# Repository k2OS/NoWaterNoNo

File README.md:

<h1>No Water, No No</h1>
See https://labitat.dk/wiki/No_Water_No_No for more information.

Eagle/ contains eagle files for the PCB

OpenSCAD/ contains the OpenSCAD drawings for the mounting brackets for the nodes + the battery compartment.

NoWaterNoNo/ contains the software for the nodes.

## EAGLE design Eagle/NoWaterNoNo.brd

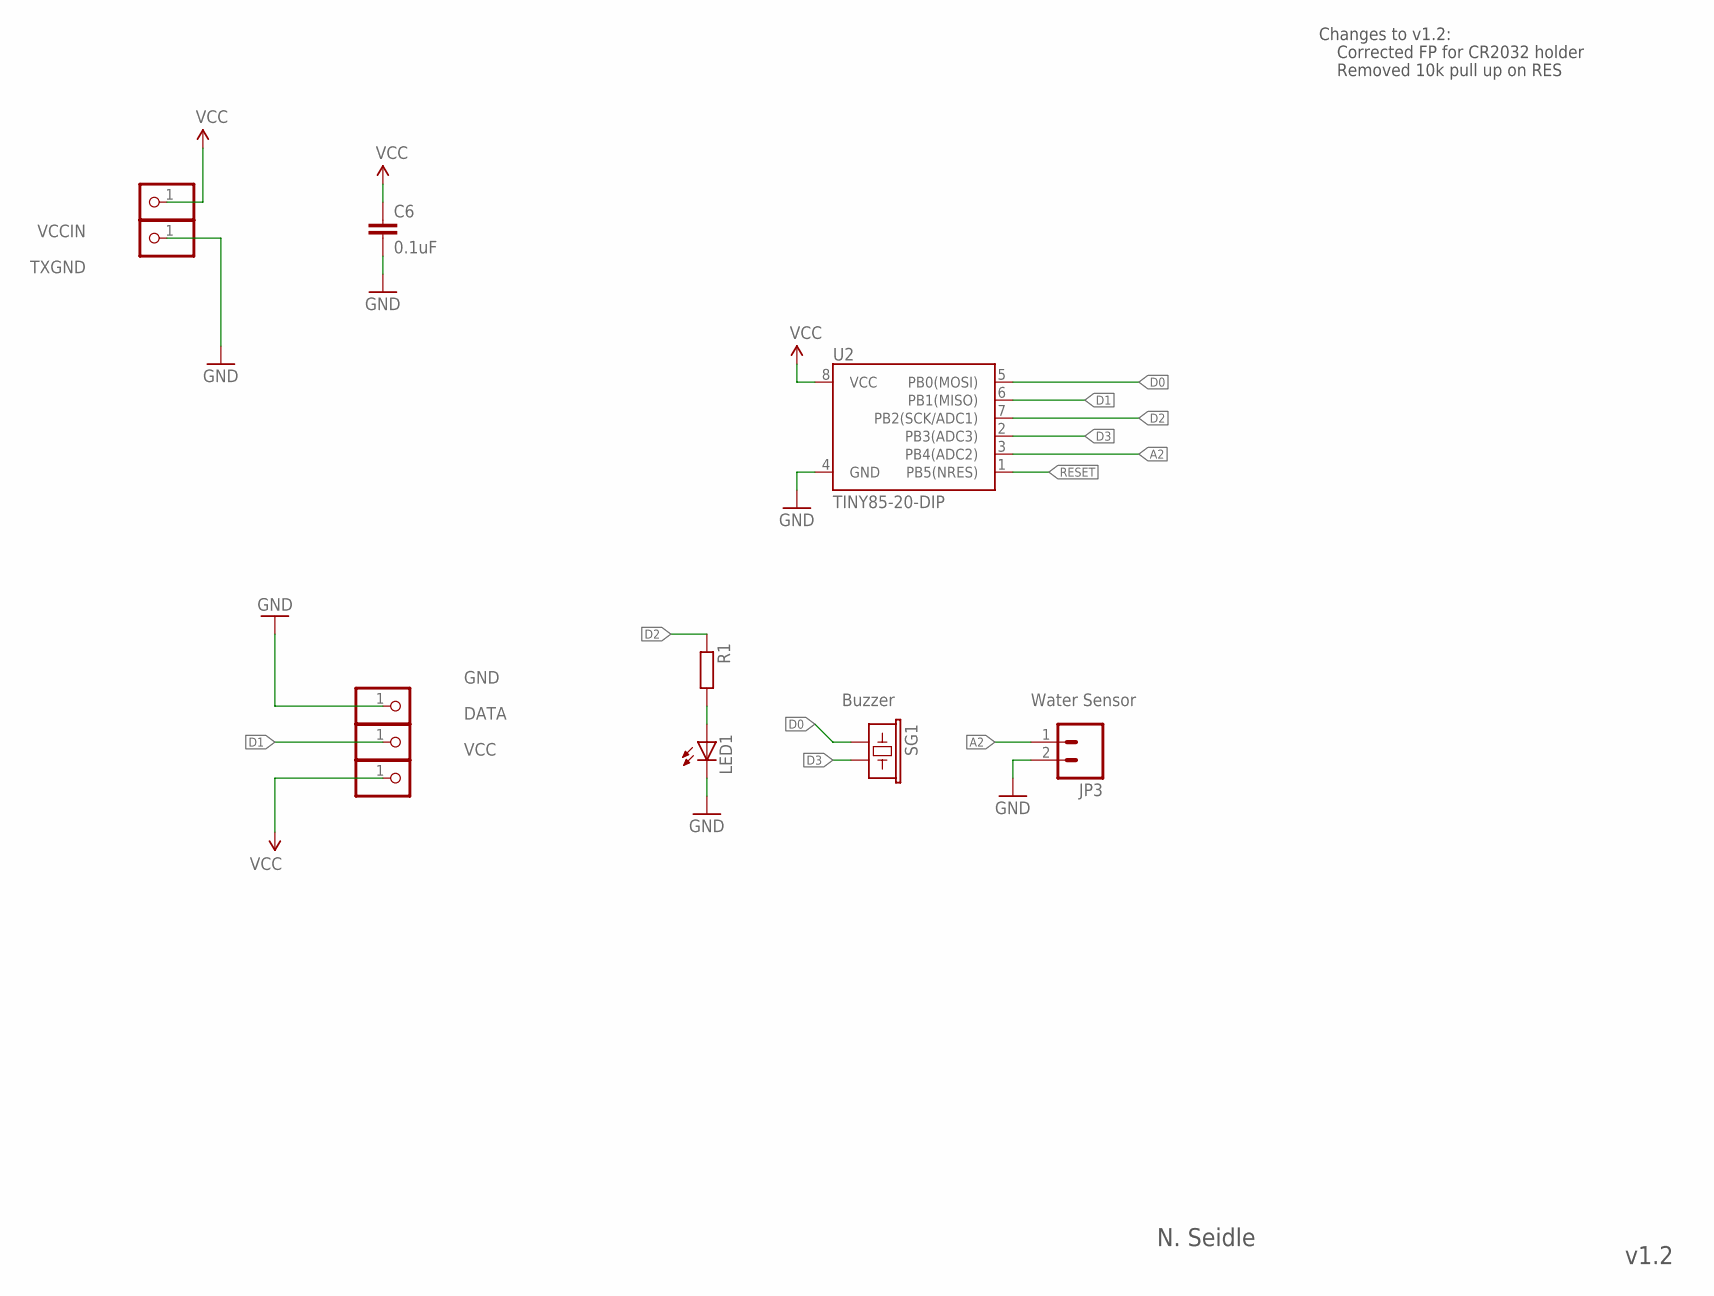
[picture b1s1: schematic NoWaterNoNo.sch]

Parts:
C6: 0.1uF; CAP-PTH-SMALL2
DATA: PINHD-1X1; 1X01
GND: PINHD-1X1; 1X01
JP3: Water Sensor; 1X02
LED1: LED5MM
R1: R-EU_0204/2V; 0204V
SG1: Buzzer; BUZZER-12MM
TXGND: PINHD-1X1; 1X01
U2: TINY85-20-DIP; DIP08
VCC: PINHD-1X1; 1X01
VCCIN: PINHD-1X1; 1X01

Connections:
A2: JP3.1, U2.3 (PB4(ADC2))
D0: SG1.+ (1), U2.5 (PB0(MOSI))
D1: DATA.1, U2.6 (PB1(MISO))
D2: R1.1, U2.7 (PB2(SCK/ADC1))
D3: SG1.- (2), U2.2 (PB3(ADC3))
GND: C6.2, GND.1, JP3.2, LED1.K (C), TXGND.1, U2.4 (GND)
unnamed: LED1.A, R1.2
RESET: U2.1 (PB5(NRES))
VCC: C6.1, U2.8 (VCC), VCC.1, VCCIN.1

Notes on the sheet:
N. Seidle
Changes to v1.2:
Corrected FP for CR2032 holder
Removed 10k pull up on RES
v1.2

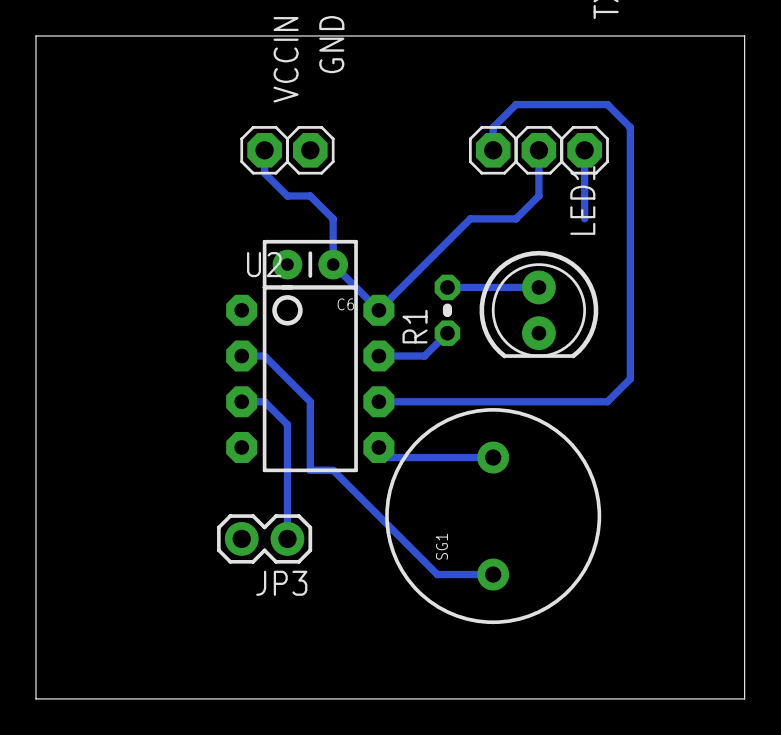
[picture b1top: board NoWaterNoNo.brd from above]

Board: 2 copper layers, 39.4 x 36.8 mm, 11 parts (0 on the bottom side), 8 nets.

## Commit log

2014-04-14 Added eagle files
2014-04-14 Adding README
2014-04-14 typo
2014-04-14 more typo
2014-04-21 Added comments
2014-09-04 Added testbranch for Eagle-files
2014-09-04 Adding openscad drawings
2014-09-04 Adding new version of node mount
2014-09-04 Typo in scad-file
2014-09-04 Eagle: BRD and SCH files from test branch were more up to date than master.
2014-10-13 Changed board layout. Buzzer, radio and sensor have changed pin assignments.
2014-10-13 Added new slimmer version of PCB-holder.
2014-10-13 Changed board layouts once again. Changes made to Arduino code as well.

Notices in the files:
parts and their libraries:
SparkFun-DigitalIC: Licensing: CC v3.0 Share-Alike You are welcome to use this library for commercial purposes.
